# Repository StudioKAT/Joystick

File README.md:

# Joystick

## 概要 / Overview

**Joystick** は、6HPサイズの片手操作に特化したマニュアルCV/Gate生成モジュールです。  
XY入力端子に外部CVを接続することで、アッテネーターやインバーターとしても利用可能です。  
CVレンジとオフセットはX軸・Y軸ごとに個別に調整でき、最大±10Vの範囲で任意のCVを生成できます。  
スティックを押し込むと、+10VのGate信号が出力されます。

**Joystick** is a 6HP manual CV/Gate generator module designed for one-handed operation.  
By connecting external CV signals to the X and Y inputs, it can also function as an attenuator or inverter.  
Each axis (X and Y) features independent control over CV range and offset, allowing for custom voltage outputs up to ±10V.  
Pressing the joystick down outputs a +10V Gate signal.

## 仕様 / Spec
- Format: Eurorack
- Function: Attenuator-Inverter joystick controller and Gate Generator.
- Current needs: +12V: 35mA, -12V: 35mA
- Width: 6 HP
- Depth: 25mm (including power connector)

## 動画 / Movie

## 販売 / Sales

StudioKATオフィシャルショップで販売しています。(日本国内限定)  
https://www.studiokat.jp/items/106541452

## ライセンス / License

この作品は [Creative Commons 表示 - 継承 4.0 国際 (CC BY-SA 4.0)](https://creativecommons.org/licenses/by-sa/4.0/deed.ja) の下でライセンスされています。  
This work is licensed under the [Creative Commons Attribution-ShareAlike 4.0 International License](https://creativecommons.org/licenses/by-sa/4.0/).

## クレジット / Credits

- Designed by : StudioKAT
- Website : https://www.studiokat.jp/
- GitHub : https://github.com/StudioKAT
- X(Twitter) : https://x.com/StudioKAT_synth
- Instagram : https://www.instagram.com/studiokat_modular/

## 更新履歴 / Changelog

- `2024-09-28` v1.0 Unreleased
- `2025-04-24` v2.0 Released
- `2025-07-02` v3.0 Released

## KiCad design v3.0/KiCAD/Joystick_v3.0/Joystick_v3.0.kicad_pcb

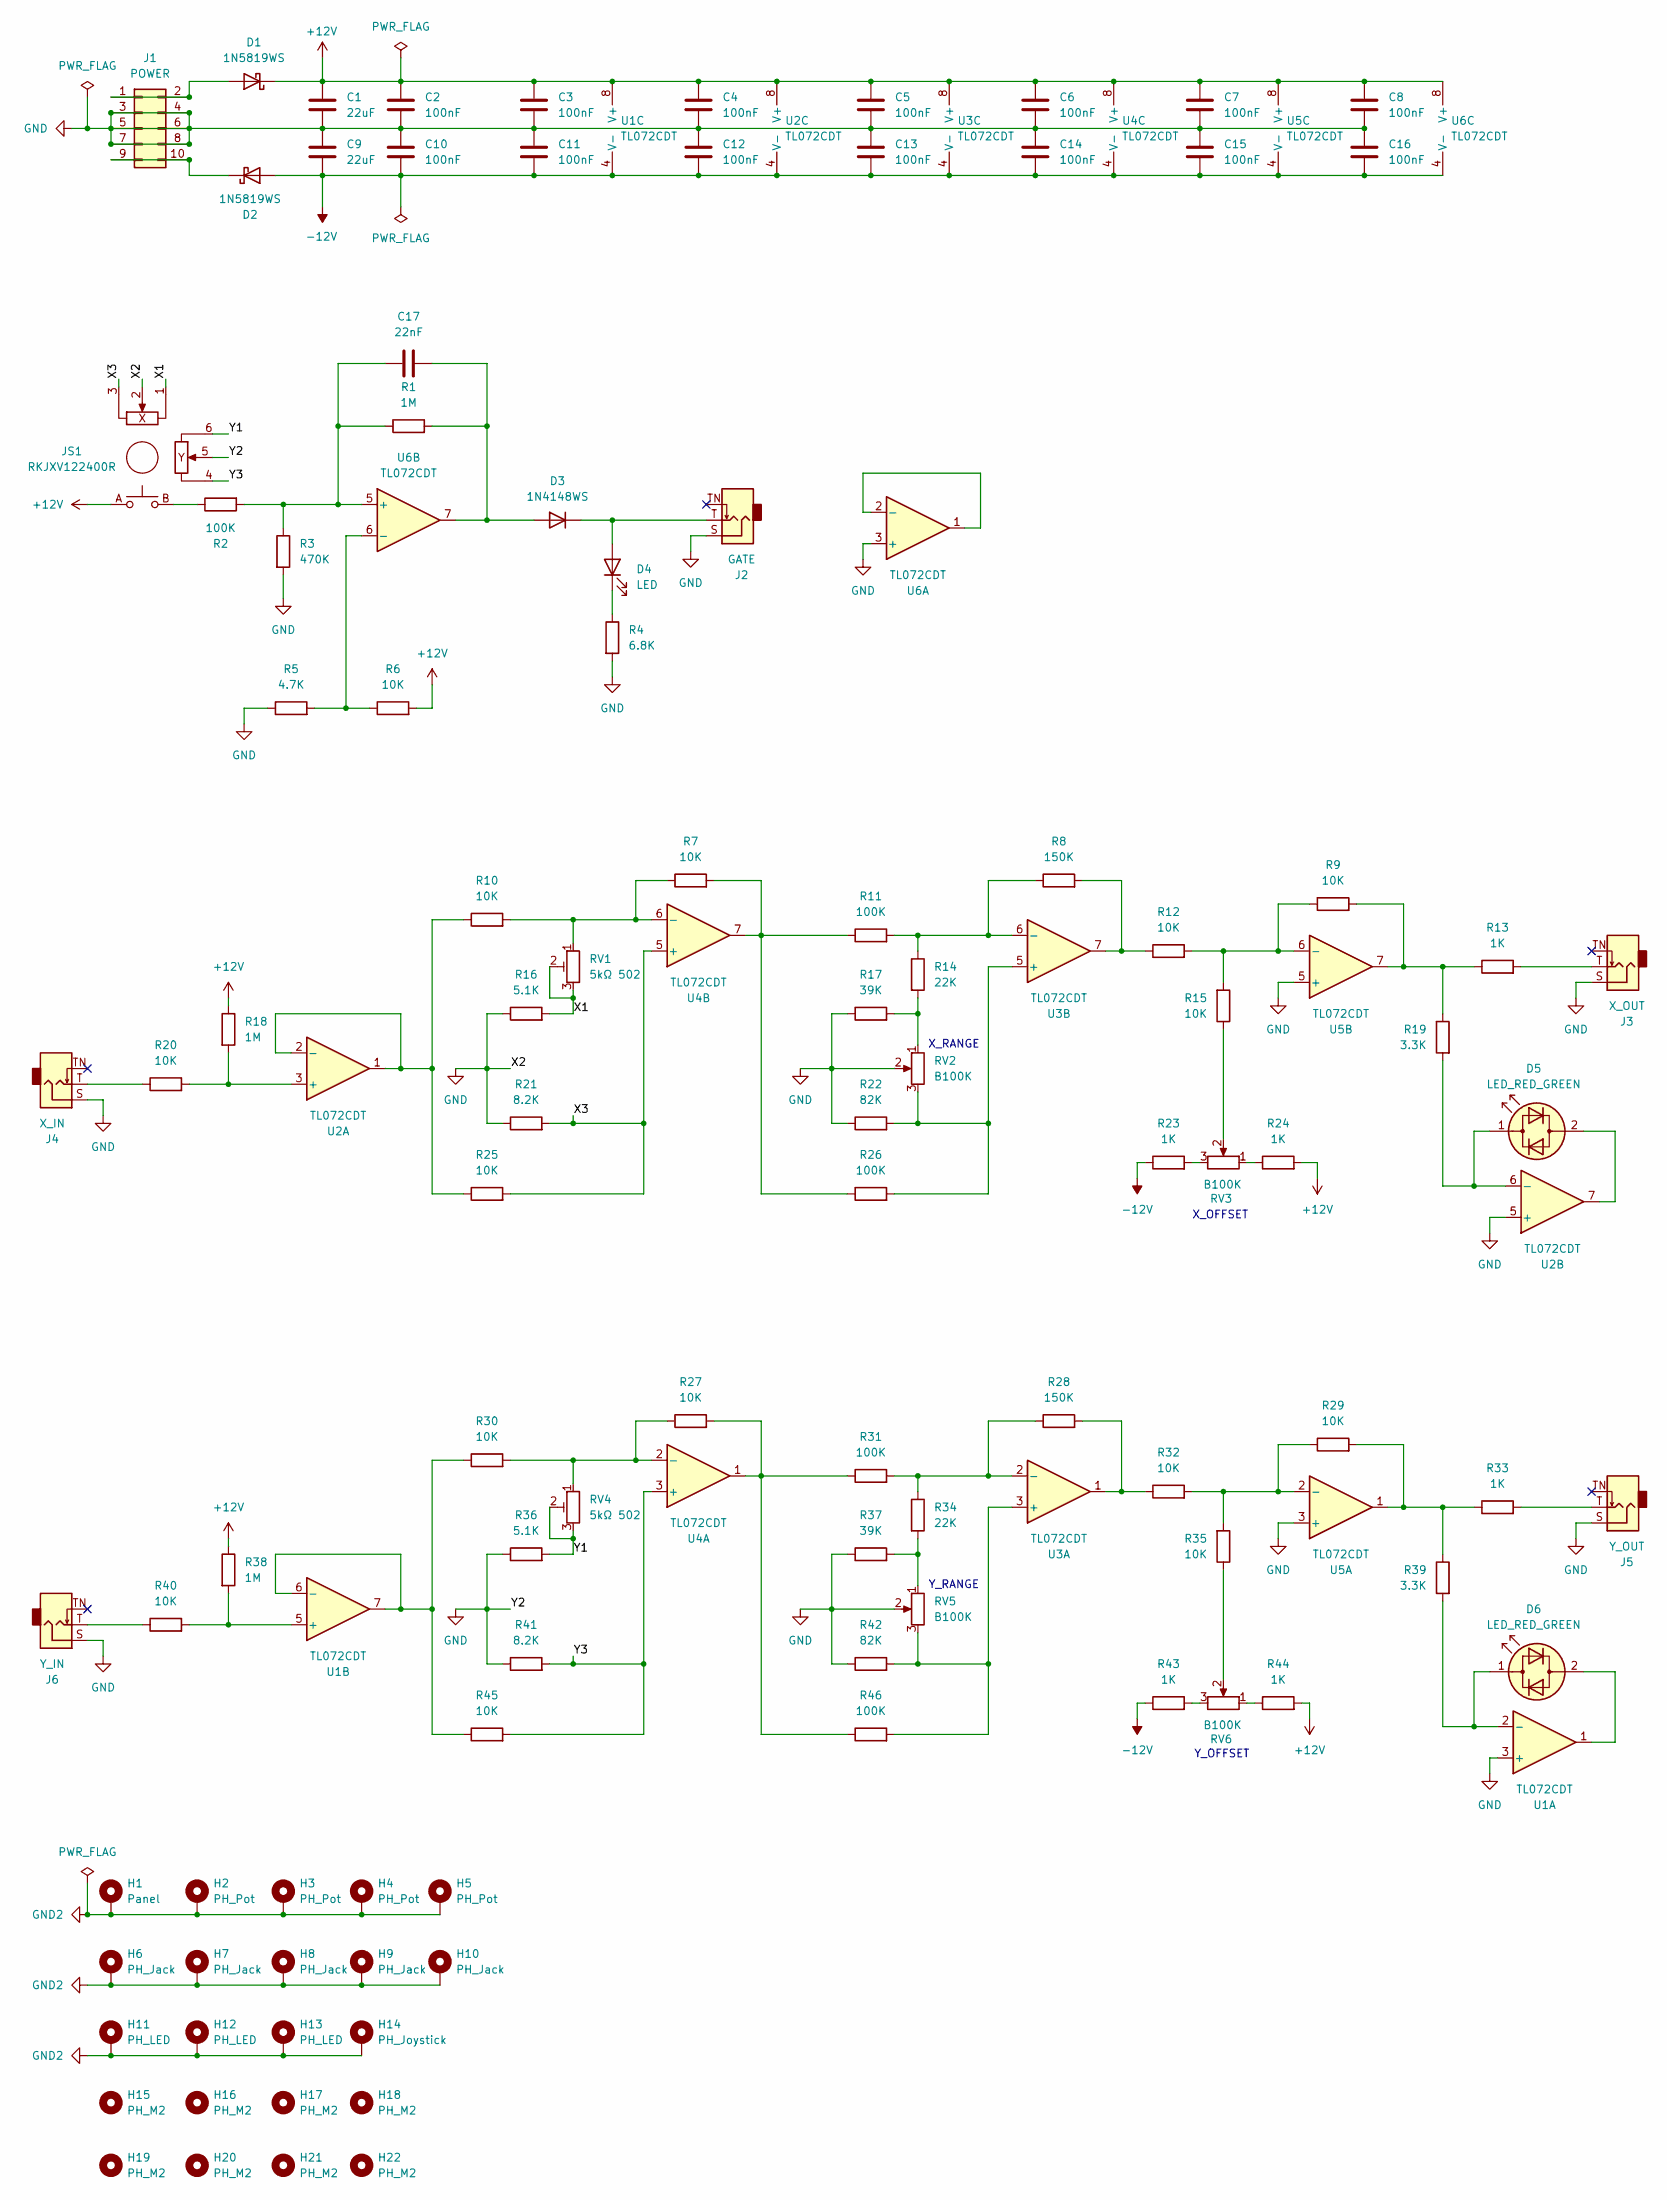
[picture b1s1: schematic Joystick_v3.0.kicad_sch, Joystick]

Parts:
C1, C9: 22uF; C_0805_2012Metric; LCSC C45783
C2, C3, C4, C5, C6, C7, C8, C10, C11, C12, C13, C14, C15, C16: 100nF; C_0603_1608Metric; LCSC C14663
C17: 22nF; C_0603_1608Metric; LCSC C21122
D1, D2: 1N5819WS; D_SOD-323; LCSC C191023
D3: 1N4148WS; D_SOD-323; LCSC C2128
D4: LED; LED_D3.0mm
D5, D6: LED_RED_GREEN; LED_D3.0mm
H1: Panel; Panel_6HP
H2, H3, H4, H5: PH_Pot; PH_RV09_center
H6, H7, H8, H9, H10: PH_Jack; PH_AudioJack_3.5mm_Pad
H11, H12, H13: PH_LED; PH_LED_3.0mm_Pad
H14: PH_Joystick
H15, H16, H17, H18, H19, H20, H21, H22: PH_M2; MountingHole_2.2mm_M2
J1: POWER; BoxHeader_2x05_2.54mm_Europower
J2: GATE; AudioJack_PJ301M-12
J3: X_OUT; AudioJack_PJ301M-12
J4: X_IN; AudioJack_PJ301M-12
J5: Y_OUT; AudioJack_PJ301M-12
J6: Y_IN; AudioJack_PJ301M-12
JS1: RKJXV122400R; Joystick_RKJXV122400R
R1, R18, R38: 1M; R_0603_1608Metric; LCSC C22935
R2, R11, R26, R31, R46: 100K; R_0603_1608Metric; LCSC C25803
R3: 470K; R_0603_1608Metric; LCSC C23178
R4: 6.8K; R_0603_1608Metric; LCSC C23212
R5: 4.7K; R_0603_1608Metric; LCSC C23162
R6, R7, R9, R10, R12, R15, R20, R25, R27, R29, R30, R32, R35, R40, R45: 10K; R_0603_1608Metric; LCSC C25804
R8, R28: 150K; R_0603_1608Metric; LCSC C22807
R13, R23, R24, R33, R43, R44: 1K; R_0603_1608Metric; LCSC C21190
R14, R34: 22K; R_0603_1608Metric; LCSC C31850
R16, R36: 5.1K; R_0603_1608Metric; LCSC C23186
R17, R37: 39K; R_0603_1608Metric; LCSC C23153
R19, R39: 3.3K; R_0603_1608Metric; LCSC C22978
R21, R41: 8.2K; R_0603_1608Metric; LCSC C25981
R22, R42: 82K; R_0603_1608Metric; LCSC C23254
RV1, RV4: 5kΩ 502; Potentiometer_Bourns_3296W_Vertical
RV2, RV3, RV5, RV6: B100K; Potentiometer_RV09
U1, U2, U3, U4, U5, U6: TL072CDT; SOIC-8_3.9x4.9mm_P1.27mm; LCSC C6961

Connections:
+12V: C1.1, C2.1, C3.1, C4.1, C5.1, C6.1, C7.1, C8.1, D1.1 (K), JS1.A, R6.2, R18.1, R24.2, R38.1, R44.2, U1.8 (V+), U2.8 (V+), U3.8 (V+), U4.8 (V+), U5.8 (V+), U6.8 (V+)
-12V: C9.2, C10.2, C11.2, C12.2, C13.2, C14.2, C15.2, C16.2, D2.2 (A), R23.1, R43.1, U1.4 (V-), U2.4 (V-), U3.4 (V-), U4.4 (V-), U5.4 (V-), U6.4 (V-)
/X1: JS1.1, R16.2, RV1.2, RV1.3
/X3: JS1.3, R21.2, R25.2, U4.5 (+)
/Y1: JS1.6, R36.2, RV4.2, RV4.3
/Y3: JS1.4, R41.2, R45.2, U4.3 (+)
GND: C1.2, C2.2, C3.2, C4.2, C5.2, C6.2, C7.2, C8.2, C9.1, C10.1, C11.1, C12.1, C13.1, C14.1, C15.1, C16.1, J1.3, J1.4, J1.5, J1.6, J1.7, J1.8, J2.S, J3.S, J4.S, J5.S, J6.S, JS1.2, JS1.5, R3.2, R4.2, R5.1, R16.1, R17.1, R21.1, R22.1, R36.1, R37.1, R41.1, R42.1, RV2.2, RV5.2, U1.3 (+), U2.5 (+), U5.3 (+), U5.5 (+), U6.3 (+)
GND2: H1.1, H2.1, H3.1, H4.1, H5.1, H6.1, H7.1, H8.1, H9.1, H10.1, H11.1, H12.1, H13.1, H14.1
unnamed: D1.2 (A), J1.1, J1.2
unnamed: D2.1 (K), J1.9, J1.10
unnamed: C17.2, D3.2 (A), R1.2, U6.7
unnamed: D3.1 (K), D4.2 (A), J2.T
unnamed: D4.1 (K), R4.1
unnamed: D5.2 (AK), U2.7
unnamed: D5.1 (KA), R19.2, U2.6 (-)
unnamed: D6.2 (AK), U1.1
unnamed: D6.1 (KA), R39.2, U1.2 (-)
unnamed: J3.T, R13.2
unnamed: J4.T, R20.1
unnamed: J5.T, R33.2
unnamed: J6.T, R40.1
unnamed: JS1.B, R2.1
unnamed: R7.2, R11.1, R26.1, U4.7
unnamed: R8.2, R12.1, U3.7
unnamed: R9.2, R13.1, R19.1, U5.7
unnamed: R14.2, R17.2, RV2.1
unnamed: R15.1, RV3.2
unnamed: R23.2, RV3.3
unnamed: R24.1, RV3.1
unnamed: R27.2, R31.1, R46.1, U4.1
unnamed: R28.2, R32.1, U3.1
unnamed: R29.2, R33.1, R39.1, U5.1
unnamed: R34.2, R37.2, RV5.1
unnamed: R35.1, RV6.2
unnamed: R43.2, RV6.3
unnamed: R44.1, RV6.1
unnamed: R38.2, R40.2, U1.5 (+)
unnamed: R30.1, R45.1, U1.6 (-), U1.7
unnamed: R18.2, R20.2, U2.3 (+)
unnamed: R10.1, R25.1, U2.1, U2.2 (-)
unnamed: R42.2, R46.2, RV5.3, U3.3 (+)
unnamed: R28.1, R31.2, R34.1, U3.2 (-)
unnamed: R22.2, R26.2, RV2.3, U3.5 (+)
unnamed: R8.1, R11.2, R14.1, U3.6 (-)
unnamed: R27.1, R30.2, RV4.1, U4.2 (-)
unnamed: R7.1, R10.2, RV1.1, U4.6 (-)
unnamed: R29.1, R32.2, R35.2, U5.2 (-)
unnamed: R9.1, R12.2, R15.2, U5.6 (-)
unnamed: U6.1, U6.2 (-)
unnamed: C17.1, R1.1, R2.2, R3.1, U6.5 (+)
unnamed: R5.2, R6.1, U6.6 (-)

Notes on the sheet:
Y_RANGE
X_OFFSET
X_RANGE
Y_OFFSET

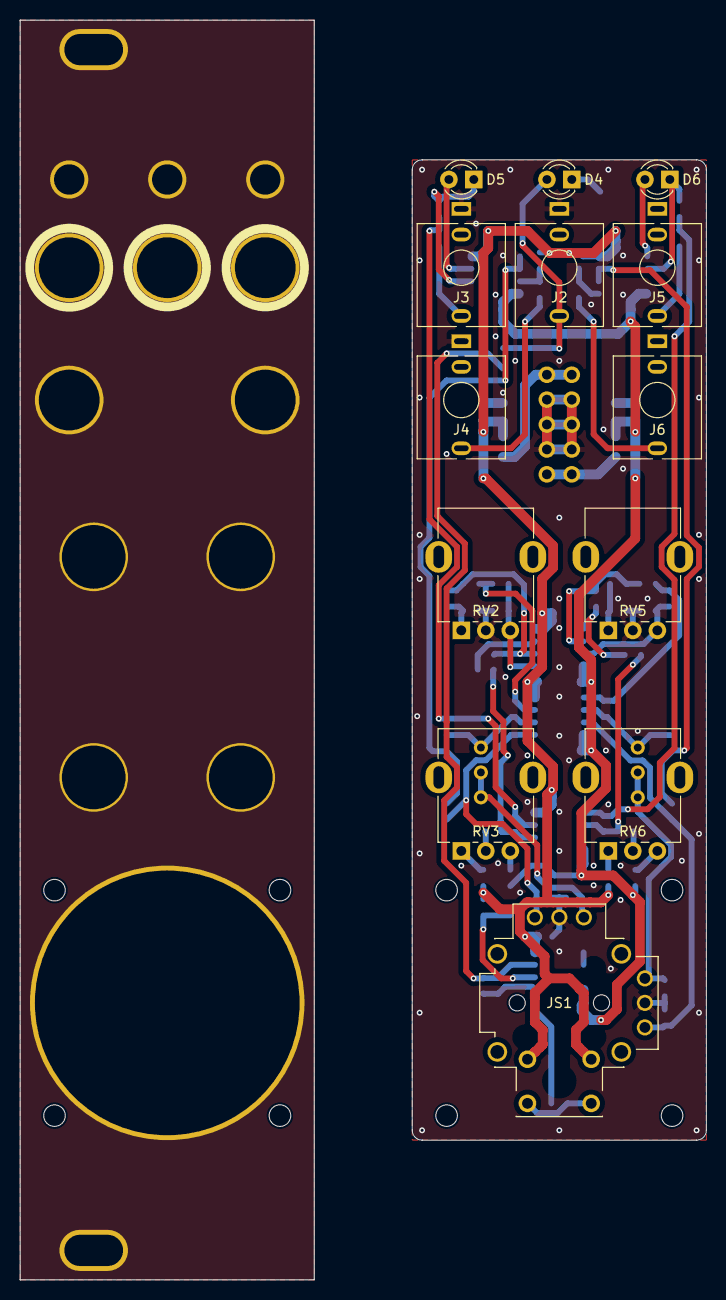
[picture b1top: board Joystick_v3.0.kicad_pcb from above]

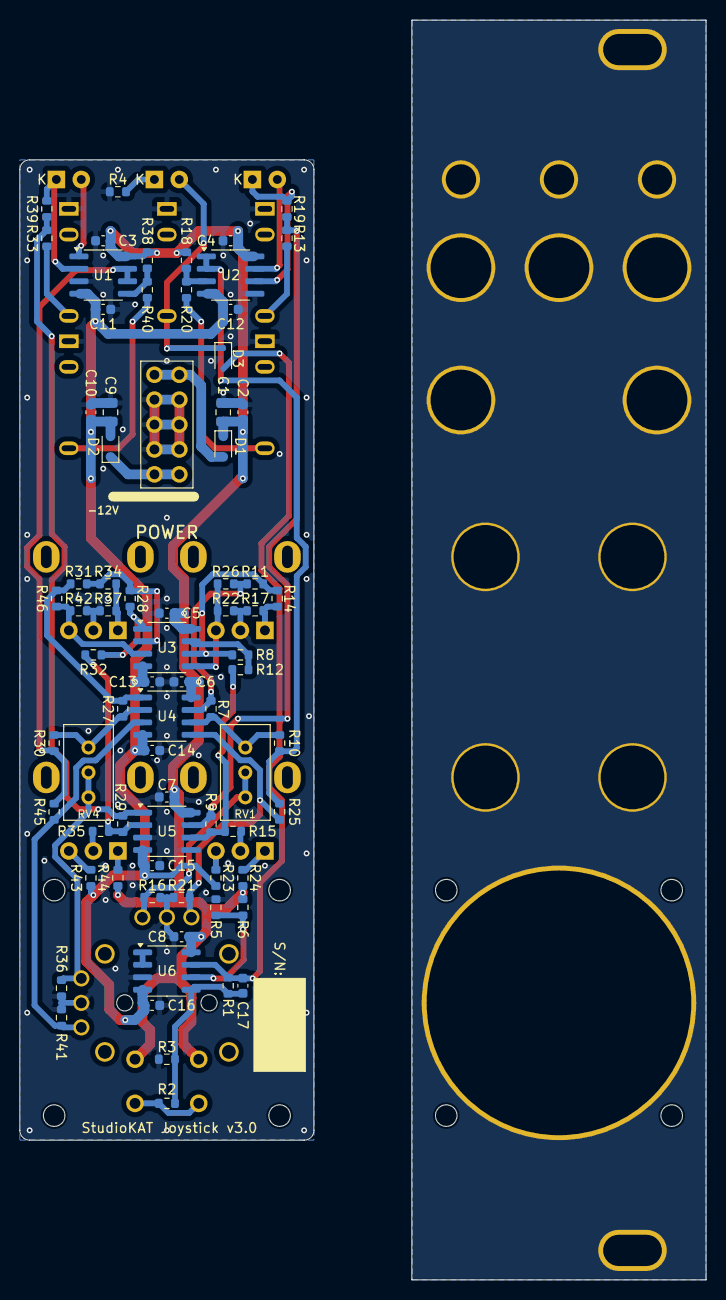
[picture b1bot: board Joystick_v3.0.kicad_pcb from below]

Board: 2 copper layers, 70.0 x 128.5 mm, 110 parts (75 on the bottom side), 51 nets.

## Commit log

2025-04-09 README.md 誤字修正
2025-04-24 マニュアル追加
2025-04-30 消費電流を実測値に変更
2025-05-18 動画追加
2025-05-22 フォルダ構成変更、KiCADプロジェクト追加
2025-05-22 README画像リンク切れ修正
2025-05-22 README画像リンク切れ修正_2
2025-05-28 画像差し替え
2025-06-08 ディレクトリ構成変更
2025-06-08 README更新
2025-06-08 フォルダ名変更
2025-07-02 v3.0追加
